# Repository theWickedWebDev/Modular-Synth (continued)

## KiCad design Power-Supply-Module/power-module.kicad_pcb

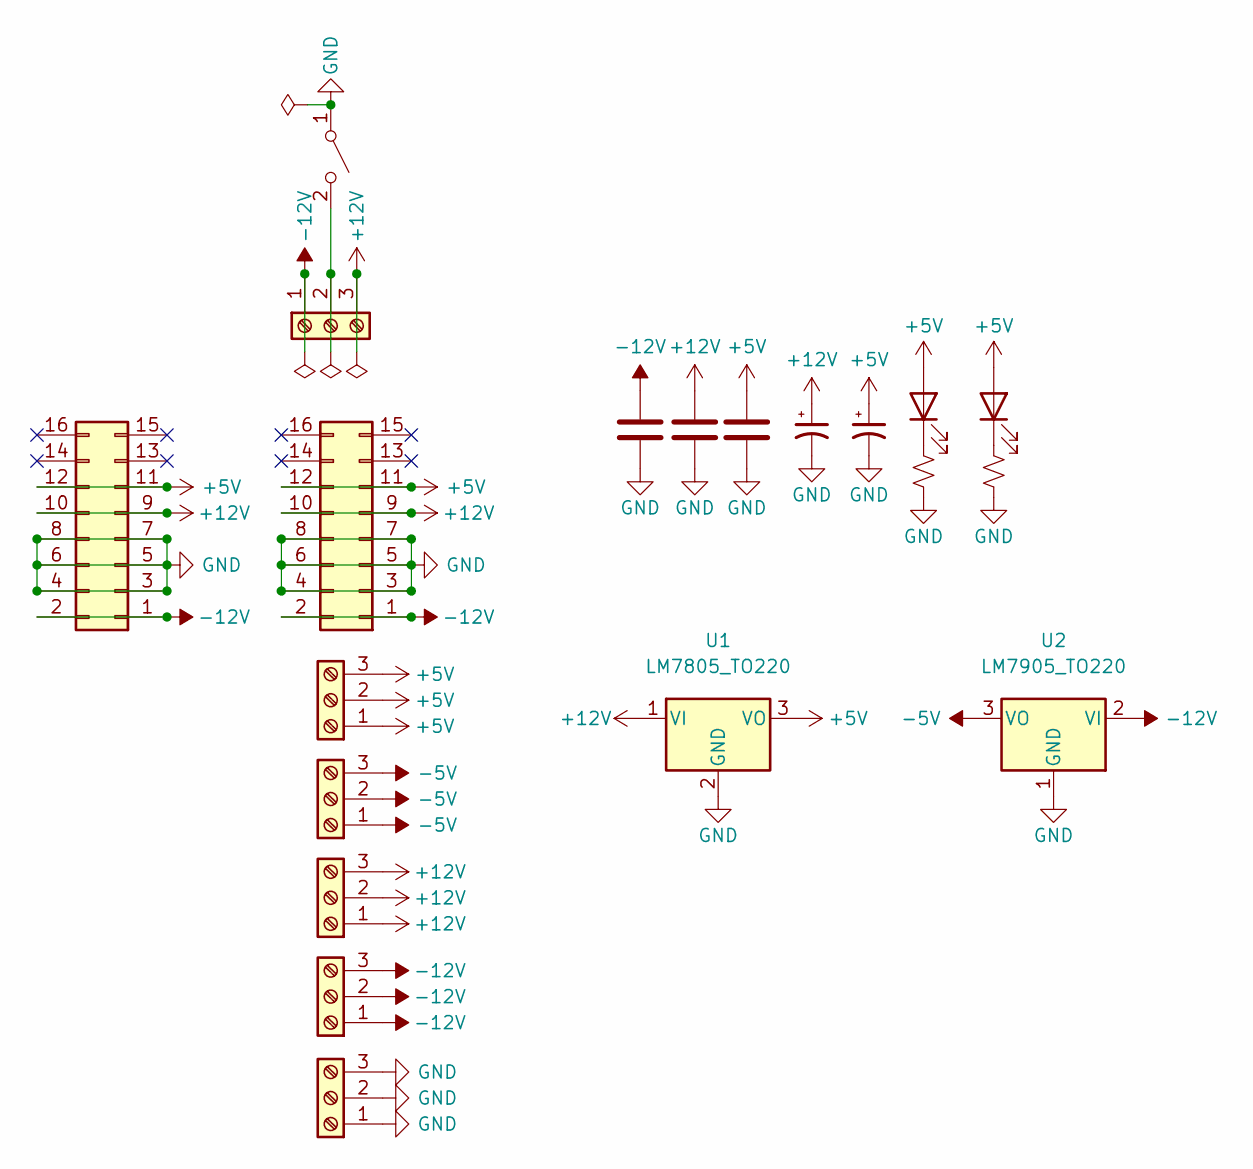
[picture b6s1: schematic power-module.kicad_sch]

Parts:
C1, C2, C3: C; C_0805_2012Metric
C4, C5: C_Polarized_Small_US; CP_Elec_6.3x7.7
D1: LED; LED_0805_2012Metric-Blue
D2: LED; LED_D3.0mm
J1, J3, J4, J5, J6, J7: Screw_Terminal_01x04; TerminalBlock_Phoenix_MKDS-1,5-3-5.08_1x03_P5.08mm_Horizont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
J2, J8: Conn_02x20_Odd_Even; IDC-Header_2x08_P2.54mm_Vertical
R1, R2: R_Small_US; R_0805_2012Metric
SW1: SW_SPST; PinHeader_1x02_P2.54mm_Vertical
U1: LM7805_TO220; TO-220-3_Vertical
U2: LM7905_TO220; TO-220-3_Vertical

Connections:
+5V: C3.1, C5.1, D1.2 (A), D2.2 (A), J2.11, J2.12, J3.1, J3.2, J3.3, J8.11, J8.12, U1.3 (VO)
+12V: C2.1, C4.1, J1.3, J2.9, J2.10, J5.1, J5.2, J5.3, J8.9, J8.10, U1.1 (VI)
-5V: J4.1, J4.2, J4.3, U2.3 (VO)
-12V: C1.1, J1.1, J2.1, J2.2, J6.1, J6.2, J6.3, J8.1, J8.2, U2.2 (VI)
GND: C1.2, C2.2, C3.2, C4.2, C5.2, J2.3, J2.4, J2.5, J2.6, J2.7, J2.8, J7.1, J7.2, J7.3, J8.3, J8.4, J8.5, J8.6, J8.7, J8.8, R1.2, R2.2, SW1.1 (A), U1.2 (GND), U2.1 (GND)
unnamed: D1.1 (K), R1.1
unnamed: D2.1 (K), R2.1
unnamed: J1.2, SW1.2 (B)

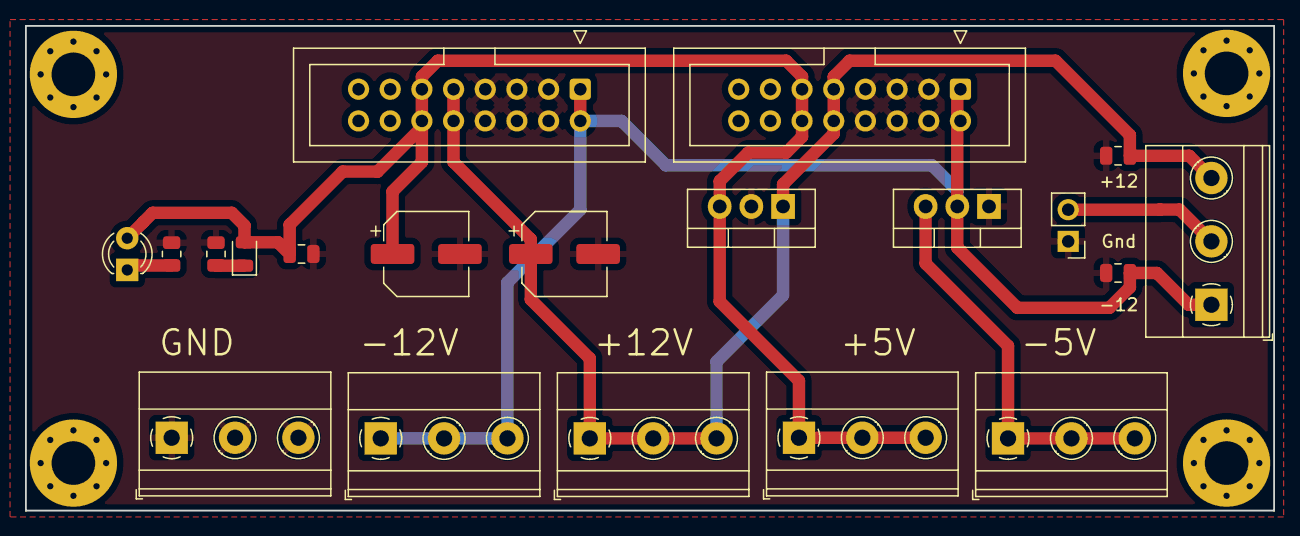
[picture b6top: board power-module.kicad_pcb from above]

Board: 2 copper layers, 100.1 x 38.9 mm, 20 parts (0 on the bottom side), 8 nets.

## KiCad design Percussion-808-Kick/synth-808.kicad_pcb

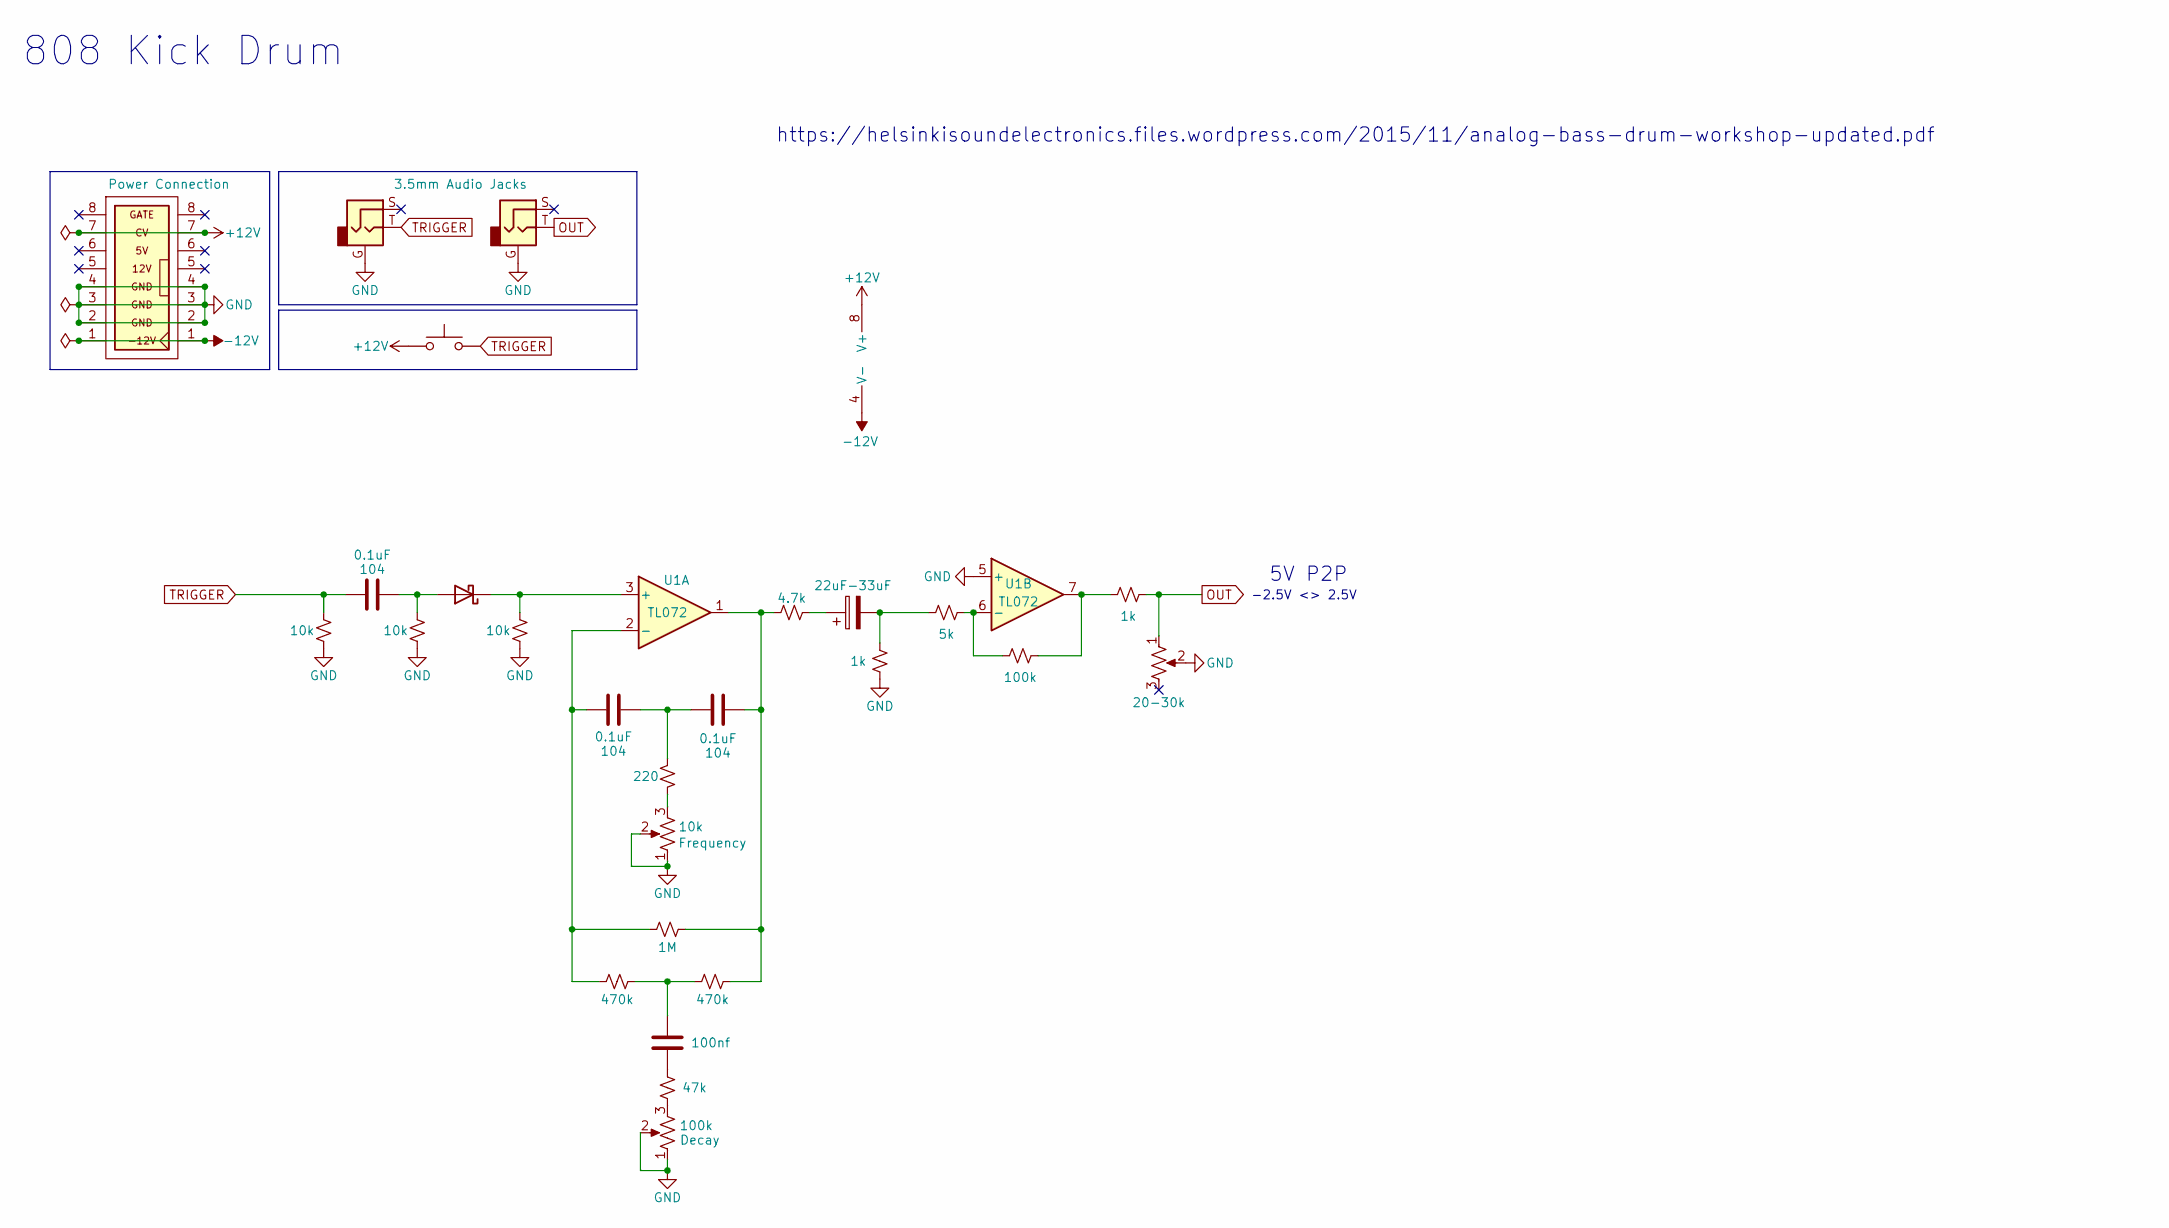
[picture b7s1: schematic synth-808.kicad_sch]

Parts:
C1, C2, C3, C5: C; C_0805_2012Metric
C4: C_Polarized; CP_Elec_5x5.4
D1: BAT54J; D_SOD-123
J1, J2: AudioJack2_Ground; 3.5mm-mono-jack-eurorack-2
R1, R2, R3, R4, R5, R6, R7, R8, R9, R10, R11, R12, R13: R_Small_US; R_0805_2012Metric
RV1, RV2: R_Potentiometer_US; alpha-9mm-potentiometer
RV3: R_Potentiometer_US; Potentiometer_Bourns_3224G_Horizontal
SW1: SW_Push; SW_PUSH_6mm
U1: TL072; SO-8_3.9x4.9mm_P1.27mm
U2: Eurorack_IDE_16P; IDC-Socket-Eurorack_16p_2.54mm

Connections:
+12V: SW1.1, U1.8 (V+), U2.7 (CV)
-12V: U1.4 (V-), U2.1 (-12V)
GND: J1.G, J2.G, R1.1, R2.1, R3.1, R9.2, RV1.1, RV1.2, RV2.1, RV2.2, RV3.2, U1.5 (+), U2.2 (GND), U2.3 (GND), U2.4 (GND)
unnamed: C1.1, D1.2 (A), R2.2
unnamed: C2.1, C3.2, R5.2
unnamed: C2.2, R6.2, R10.2, U1.2 (-)
unnamed: C3.1, R6.1, R8.2, R12.1, U1.1
unnamed: C4.1, R8.1
unnamed: C4.2, R4.1, R9.1
unnamed: C5.1, R10.1, R12.2
unnamed: C5.2, R11.1
unnamed: D1.1 (K), R3.2, U1.3 (+)
unnamed: R4.2, R7.1, U1.6 (-)
unnamed: R5.1, RV1.3
unnamed: R11.2, RV2.3
unnamed: R7.2, R13.1, U1.7
OUT: J2.T, R13.2, RV3.1
TRIGGER: C1.2, J1.T, R1.2, SW1.2

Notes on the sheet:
5V P2P
808 Kick Drum
-2.5V <> 2.5V
https://helsinkisoundelectronics.files.wordpress.com/2015/11/analog-bass-drum-workshop-updated.pdf

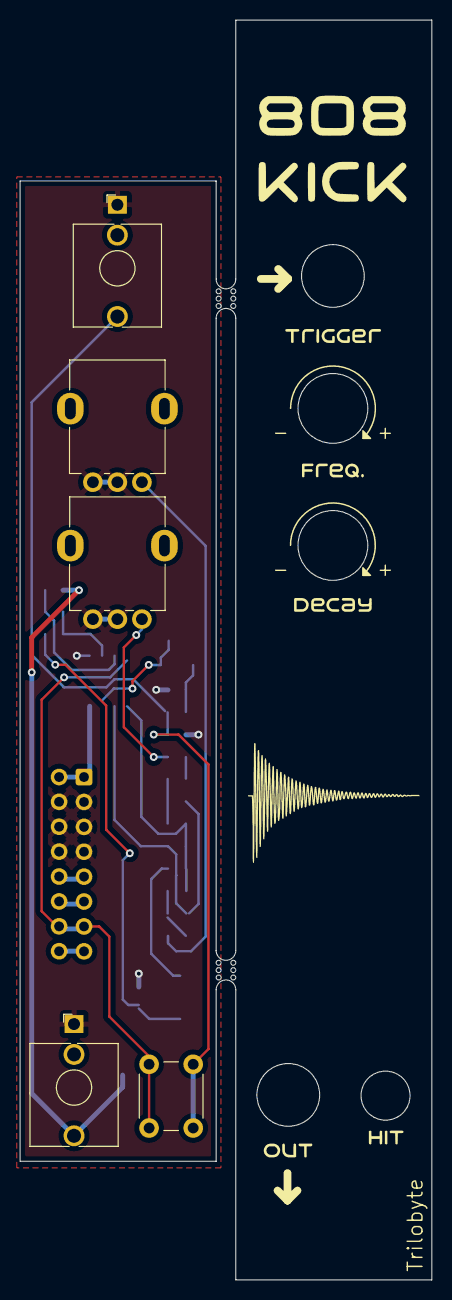
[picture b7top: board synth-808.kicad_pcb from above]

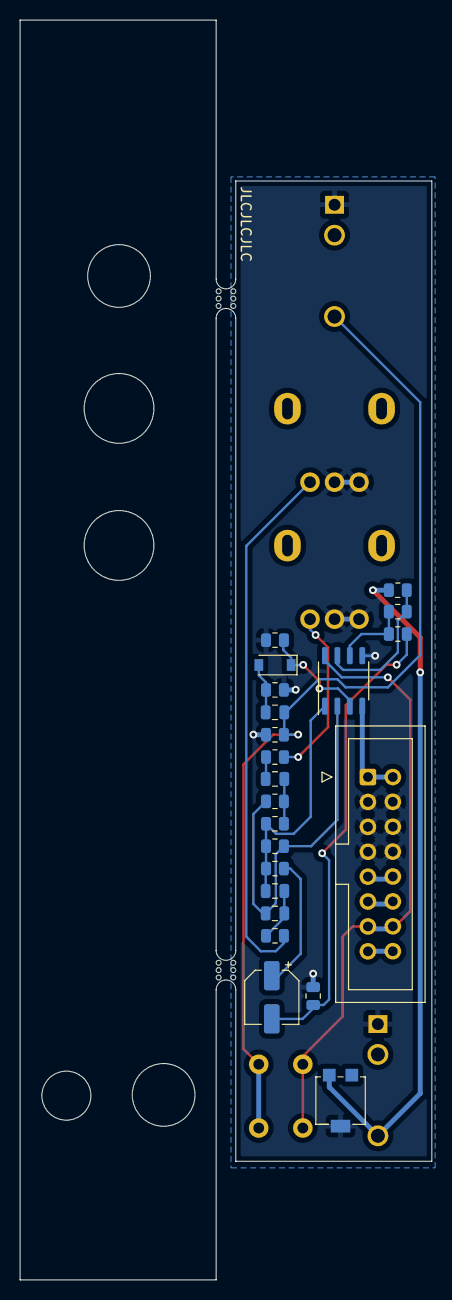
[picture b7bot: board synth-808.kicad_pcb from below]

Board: 2 copper layers, 42.0 x 128.5 mm, 31 parts (22 on the bottom side), 18 nets.

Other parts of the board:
H1, H2: MountingHole; 3.2mm-mounting-hole-eurorack
mouse-bite-2mm-slot, mouse-bite-2mm-slot#2: VAL**; mouse-bite-2mm-slot

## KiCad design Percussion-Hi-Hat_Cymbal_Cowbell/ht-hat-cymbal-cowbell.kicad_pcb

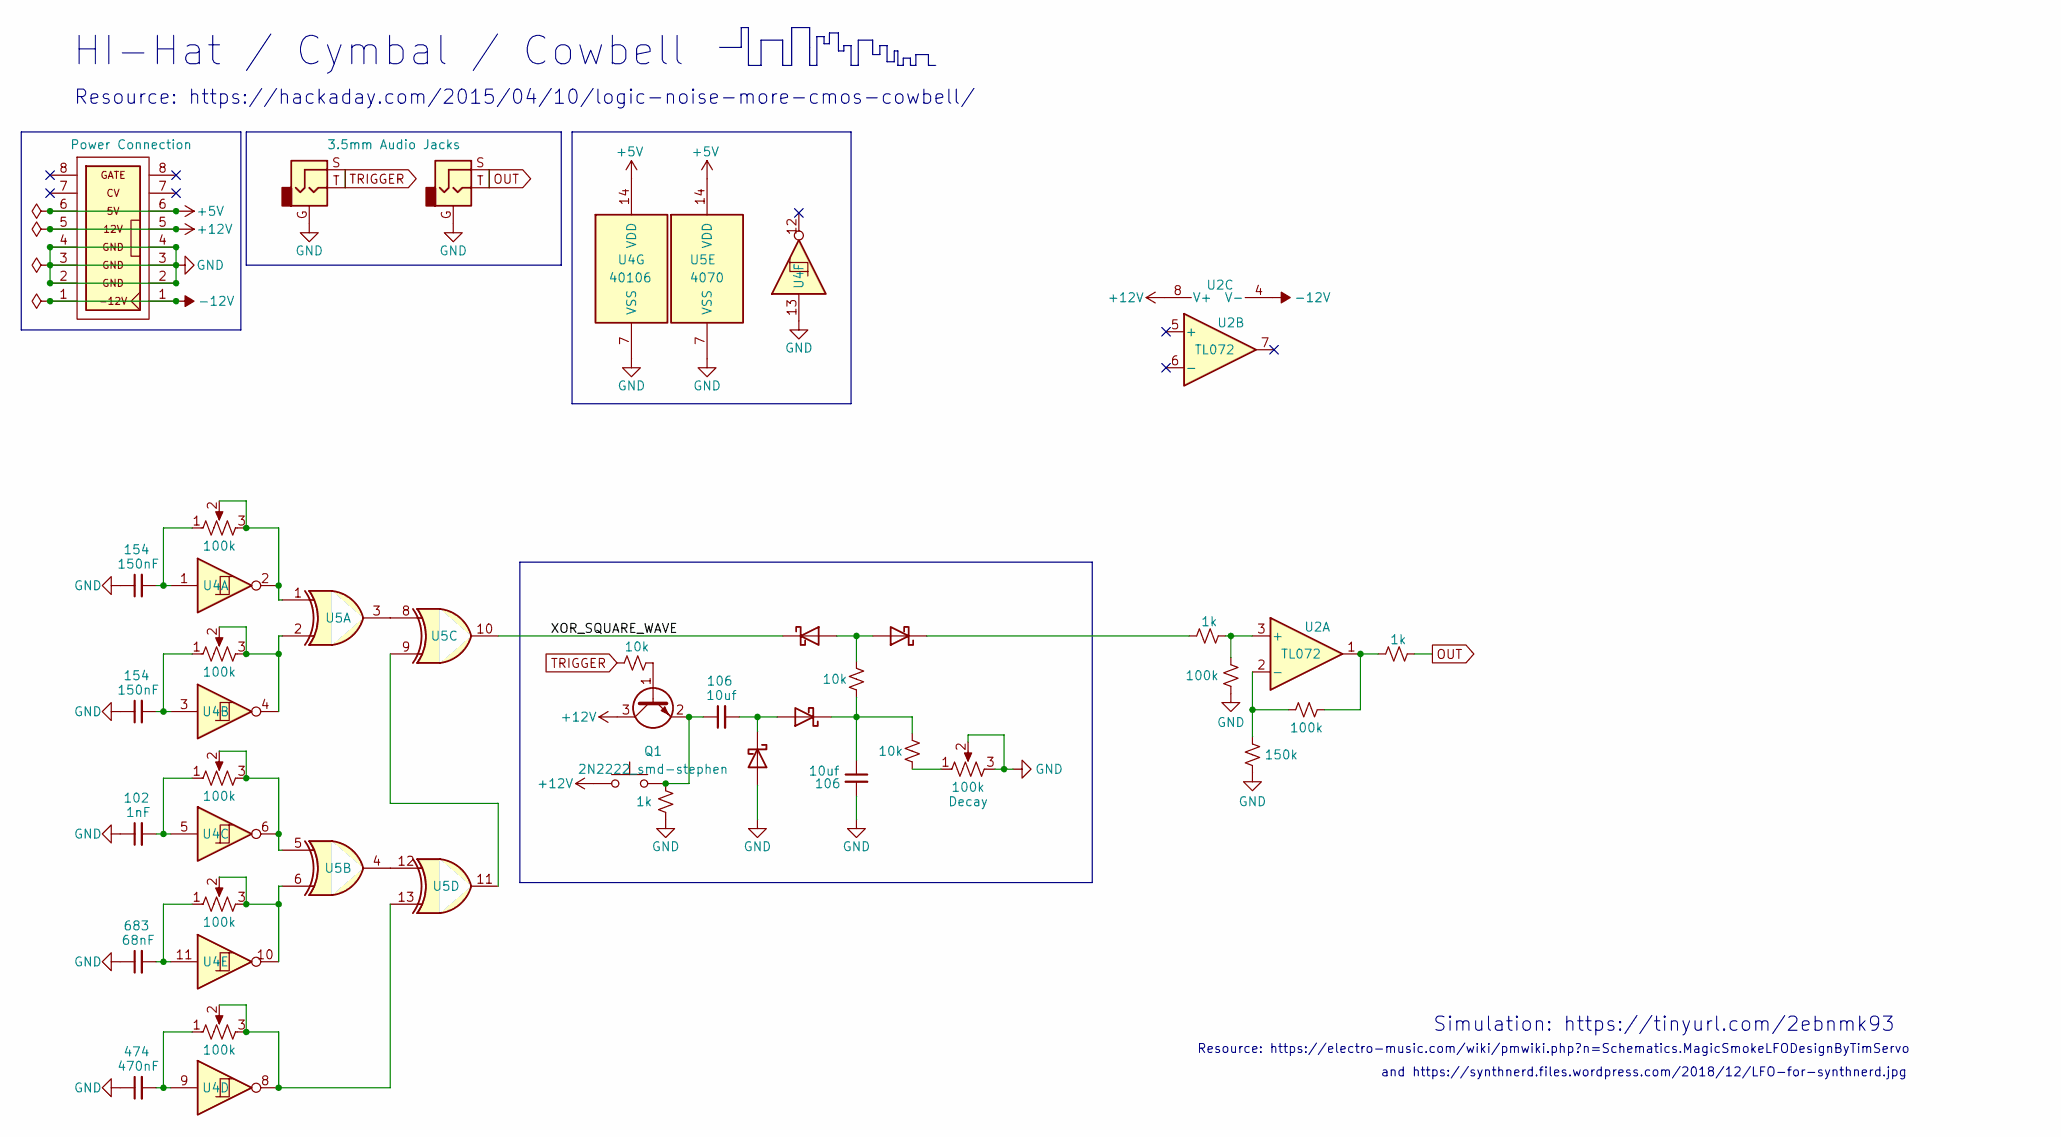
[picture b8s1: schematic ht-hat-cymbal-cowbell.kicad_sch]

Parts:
C1, C2, C3, C4, C5, C7, C8: C_Small; C_0805_2012Metric
D1, D2, D3, D4: BAT43W-V; D_SOD-123
J1, J2: AudioJack2_Ground; 3.5mm-mono-jack-eurorack-2
Q1: 2N2222_smd-stephen; SOT-23
R1, R2, R3, R4, R5, R6, R7, R8, R9: R_Small_US; R_0805_2012Metric
RV1, RV2, RV3, RV4, RV5, RV6: R_Potentiometer_US; alpha-9mm-potentiometer
SW1: SW_Push; SW_PUSH_6mm
U1: Eurorack_IDE_16P; IDC-Socket-Eurorack_16p_2.54mm
U2: TL072; SOIC-8_3.9x4.9mm_P1.27mm
U4: 40106; SOIC-14_3.9x8.7mm_P1.27mm
U5: 4070; SOIC-14_3.9x8.7mm_P1.27mm

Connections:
+5V: U1.6 (5V), U4.14 (VDD), U5.14 (VDD)
+12V: Q1.3 (C), SW1.1, U1.5 (12V), U2.8 (V+)
-12V: U1.1 (-12V), U2.4 (V-)
/XOR_SQUARE_WAVE: D3.1 (K), U5.10
GND: C1.1, C2.1, C3.1, C4.1, C5.1, C8.2, D1.2 (A), J1.G, J2.G, R1.1, R3.2, R4.1, RV1.2, RV1.3, U1.2 (GND), U1.3 (GND), U1.4 (GND), U4.7 (VSS), U4.13, U5.7 (VSS)
unnamed: C1.2, RV2.1, U4.1
unnamed: C2.2, RV3.1, U4.3
unnamed: C3.2, RV4.1, U4.5
unnamed: C4.2, RV5.1, U4.11
unnamed: C5.2, RV6.1, U4.9
unnamed: C7.1, Q1.2 (E), R1.2, SW1.2
unnamed: C7.2, D1.1 (K), D2.2 (A)
unnamed: C8.1, D2.1 (K), R5.1, R6.2
unnamed: D3.2 (A), D4.2 (A), R5.2
unnamed: D4.1 (K), R2.2
unnamed: Q1.1 (B), R9.1
unnamed: R2.1, R3.1, U2.3 (+)
unnamed: R4.2, R7.2, U2.2 (-)
unnamed: R6.1, RV1.1
unnamed: R7.1, R8.2, U2.1
unnamed: RV2.2, RV2.3, U4.2, U5.1
unnamed: RV3.2, RV3.3, U4.4, U5.2
unnamed: RV4.2, RV4.3, U4.6, U5.5
unnamed: RV5.2, RV5.3, U4.10, U5.6
unnamed: RV6.2, RV6.3, U4.8, U5.13
unnamed: U5.3, U5.8
unnamed: U5.9, U5.11
unnamed: U5.4, U5.12
OUT: J2.S, J2.T, R8.1
TRIGGER: J1.S, J1.T, R9.2

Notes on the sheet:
HI-Hat / Cymbal / Cowbell
Resource: https://electro-music.com/wiki/pmwiki.php?n=Schematics.MagicSmokeLFODesignByTimServo
Resource: https://hackaday.com/2015/04/10/logic-noise-more-cmos-cowbell/
and https://synthnerd.files.wordpress.com/2018/12/LFO-for-synthnerd.jpg
Simulation: https://tinyurl.com/2ebnmk93

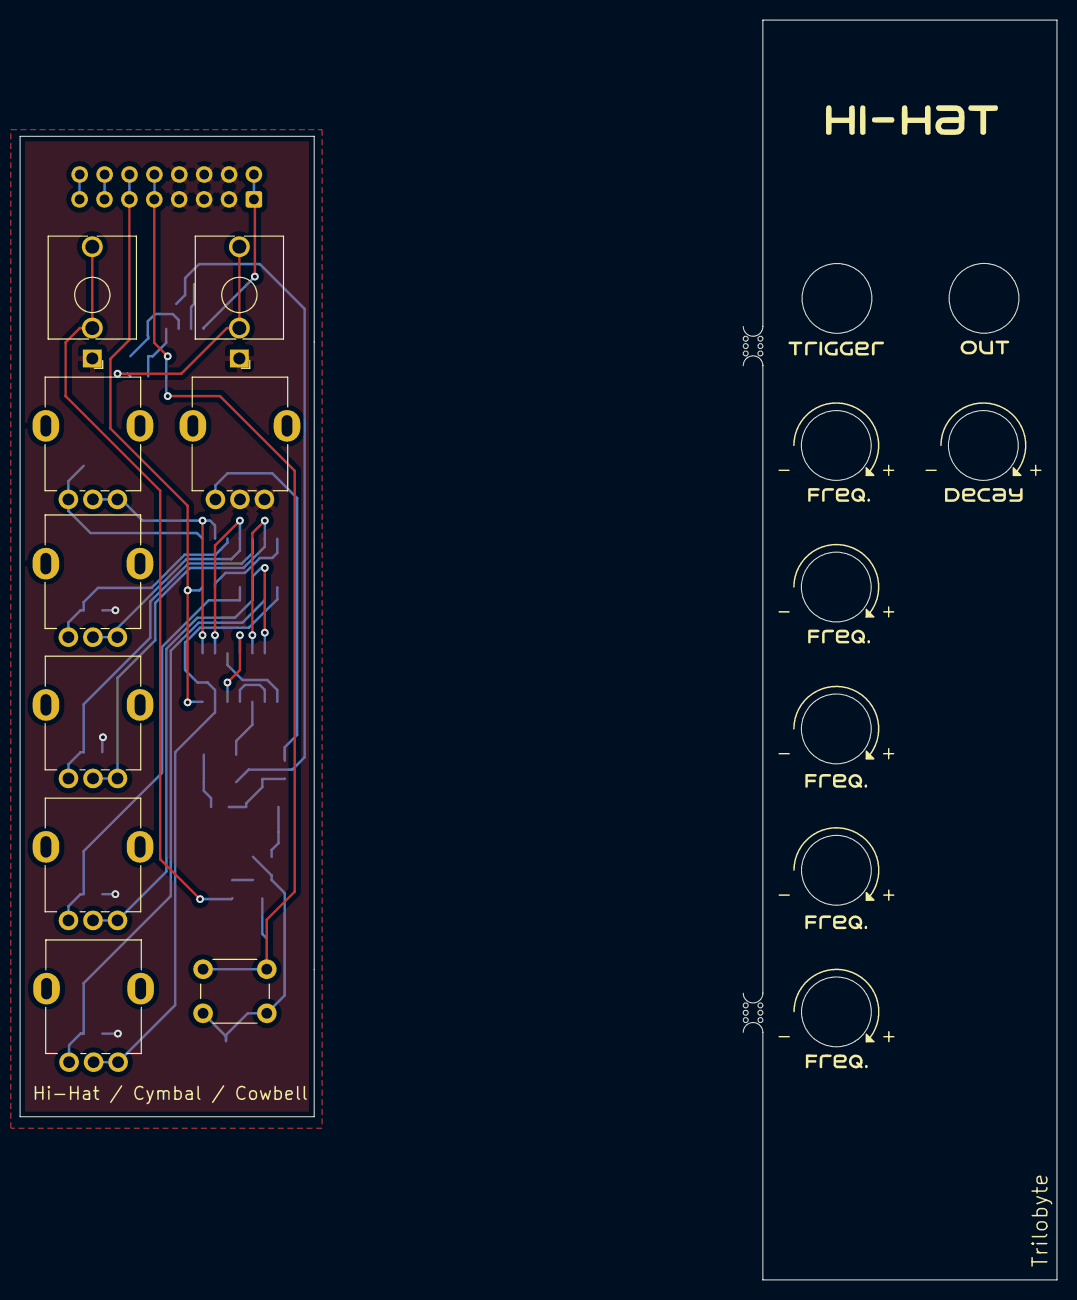
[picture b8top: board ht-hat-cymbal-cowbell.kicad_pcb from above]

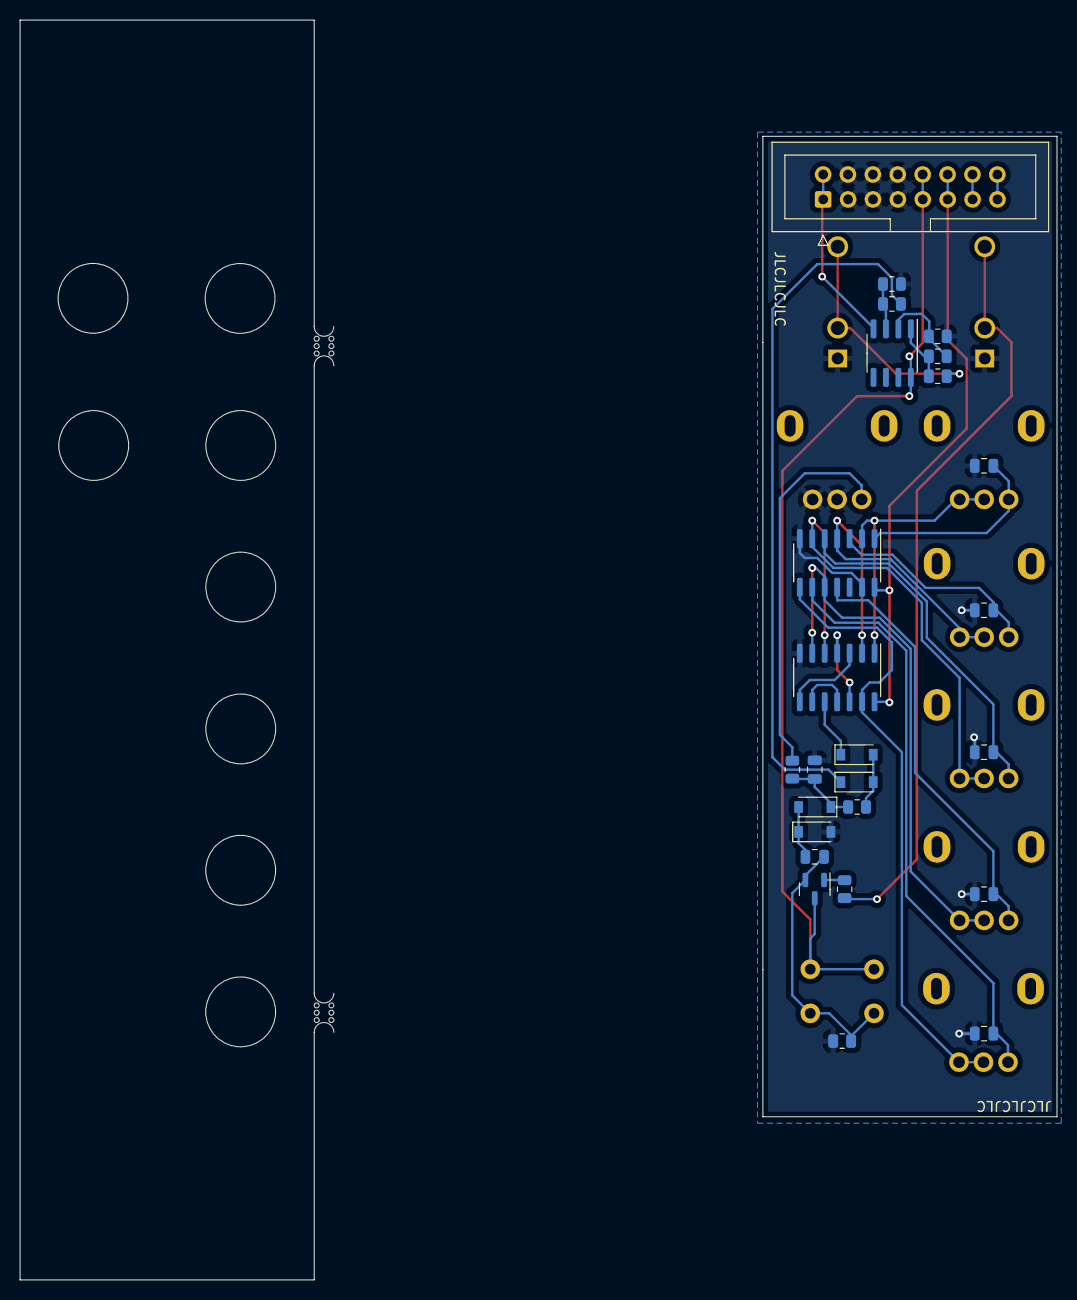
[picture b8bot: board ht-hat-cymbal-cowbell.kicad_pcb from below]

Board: 2 copper layers, 105.8 x 128.5 mm, 40 parts (25 on the bottom side), 30 nets.

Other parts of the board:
H1, H1#2, H1#3, H1#4: MountingHole; 3.2mm-mounting-hole-eurorack
mouse-bite-2mm-slot, mouse-bite-2mm-slot#2: VAL**; mouse-bite-2mm-slot

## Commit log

2022-11-15 Voltage Controlled Oscillator - New
2022-11-30 Breakout Boards
2022-11-30 Add Breakout Potentiometer images
2022-11-30 Updated Breakout Images
2022-11-30 Power Distribution
2022-12-01 Update AudioJack breakout board post fabrication issues
2022-12-05 LFO Module Addition
2022-12-14 Backing up - Files not production ready or completed
